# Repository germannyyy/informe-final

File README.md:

# informe-final
## INTEGRANTES:
German Dabundo
Patricio Luna 
Tomas Morales
Ezequiel Rios
Lucas Torrico
## FUNCIONAMIENTO
Nuestro proyecto es un calentador que trabaja con un sensor de temperatura 18b20 que le da la info a la raspberry pi pico, el calentador irá cambiando de estado hasta llegar a la temperatura deseada.
## LISTA DE MATERIALES
Raspberry Pi Pico
2 transistores BC337
Calentador de auto
Fuente de corriente continua
Sensor de temperatura 18B20
Rele 5V
LED
3 Resistencias 
Cables

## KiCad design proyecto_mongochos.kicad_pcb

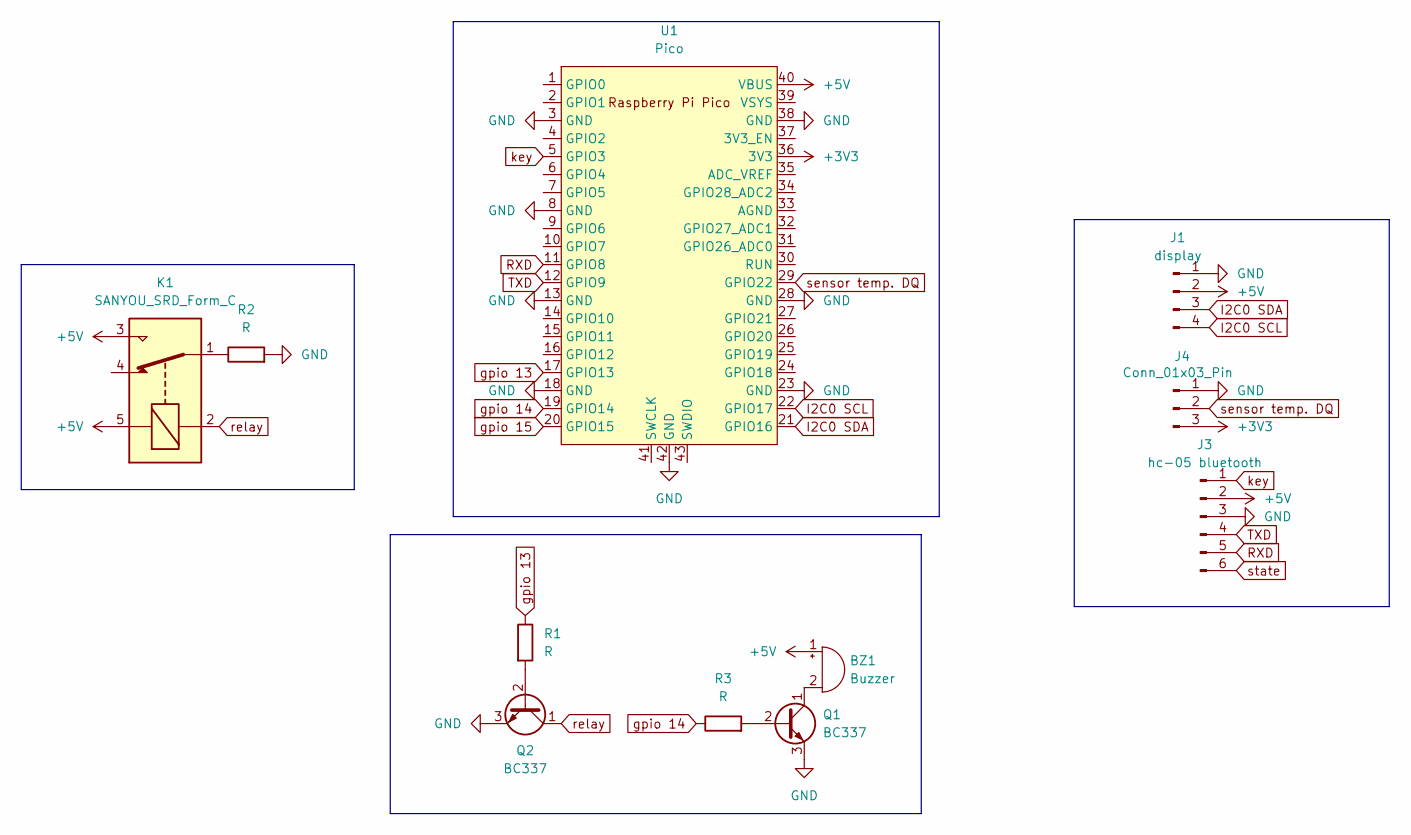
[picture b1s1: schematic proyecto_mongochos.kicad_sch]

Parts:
BZ1: Buzzer; Buzzer_D14mm_H7mm_P10mm
J1: display; PinHeader_1x04_P2.54mm_Vertical
J3: hc-05 bluetooth; PinHeader_1x06_P2.54mm_Vertical
J4: Conn_01x03_Pin; PinHeader_1x03_P2.54mm_Vertical
K1: SANYOU_SRD_Form_C; Relay_SPDT_SANYOU_SRD_Series_Form_C
Q1, Q2: BC337; TO-92_Inline
R1, R2, R3: R; R_Axial_DIN0207_L6.3mm_D2.5mm_P7.62mm_Horizontal
U1: Pico; RPi_Pico_SMD_TH

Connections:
+3V3: J4.3, U1.36 (3V3)
+5V: BZ1.1 (+), J1.2, J3.2, K1.3, K1.5, U1.40 (VBUS)
GND: J1.1, J3.3, J4.1, Q1.3 (E), Q2.3 (E), R2.2, U1.3 (GND), U1.8 (GND), U1.13 (GND), U1.18 (GND), U1.23 (GND), U1.28 (GND), U1.38 (GND), U1.42 (GND)
I2C0 SCL: J1.4, U1.22 (GPIO17)
I2C0 SDA: J1.3, U1.21 (GPIO16)
unnamed: BZ1.2 (-), Q1.1 (C)
unnamed: K1.1, R2.1
unnamed: Q1.2 (B), R3.2
unnamed: Q2.2 (B), R1.2
RXD: J3.5, U1.11 (GPIO8)
TXD: J3.4, U1.12 (GPIO9)
gpio 13: R1.1, U1.17 (GPIO13)
gpio 14: R3.1, U1.19 (GPIO14)
gpio 15: U1.20 (GPIO15)
key: J3.1, U1.5 (GPIO3)
relay: K1.2, Q2.1 (C)
sensor temp. DQ: J4.2, U1.29 (GPIO22)
state: J3.6

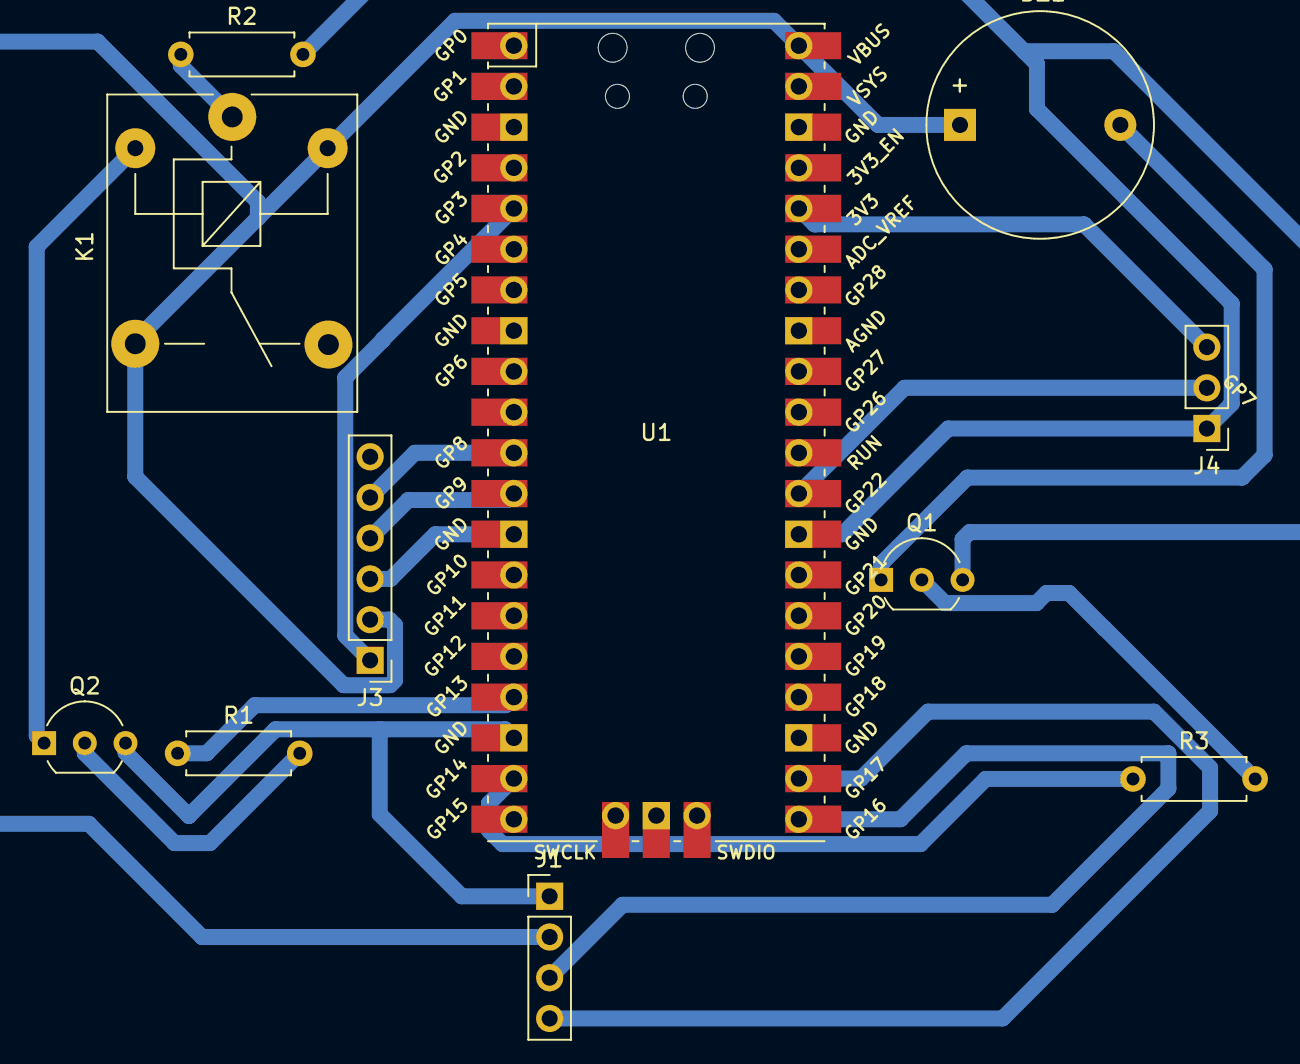
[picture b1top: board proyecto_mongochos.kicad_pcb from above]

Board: 2 copper layers, 11 parts (0 on the bottom side), 16 nets.
